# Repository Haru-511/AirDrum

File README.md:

# AirDrum
¿Alguna vez haz querido poder tocar la bateria sin necesidad de tener una bateria?

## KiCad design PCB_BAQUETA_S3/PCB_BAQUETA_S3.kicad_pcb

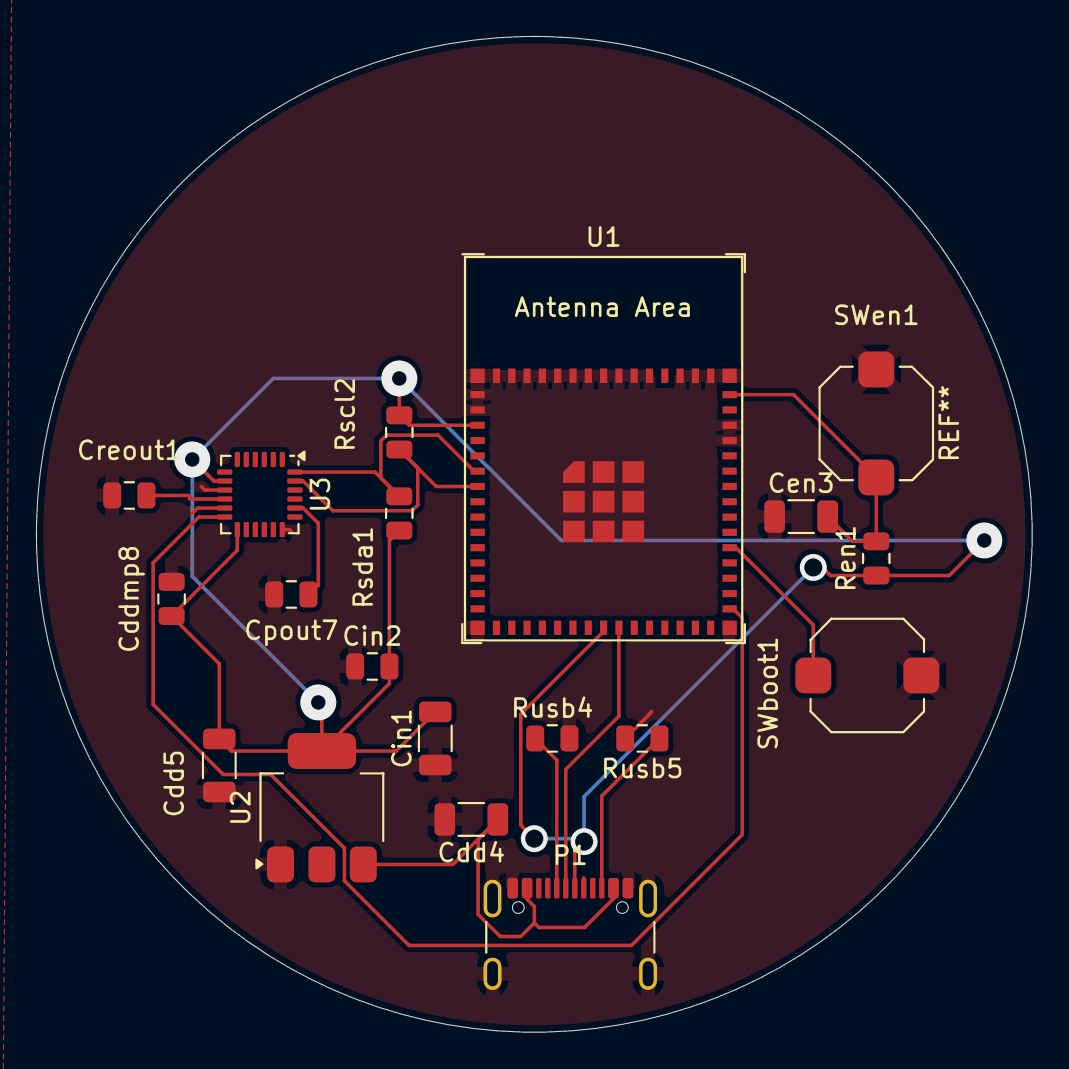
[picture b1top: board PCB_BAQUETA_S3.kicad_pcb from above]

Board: 2 copper layers, 55.3 x 55.3 mm, 19 parts (0 on the bottom side), 13 nets.

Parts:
Cdd4, Cdd5: 22u; C_1206_3216Metric
Cddmp8: 0.1u; C_0805_2012Metric
Cen3: 1u; C_1206_3216Metric
Cin1: 22u; C_1206_3216Metric
Cin2: 0.1; C_0805_2012Metric
Cpout7: 2.2n; C_0805_2012Metric
Creout1: 0.1u; C_0805_2012Metric
P1: USB_C_Plug_USB2.0; USB_C_Receptacle_GCT_USB4105-xx-A_16P_TopMnt_Horizontal
Ren1: 10k; C_0805_2012Metric
Rscl2: 4.7k; C_0805_2012Metric
Rsda1: 4.7k; C_0805_2012Metric
Rusb4, Rusb5: 5.1k; C_0805_2012Metric
SWboot1: SW_Push; SW_Push_1TS009xxxx-xxxx-xxxx_6x6x5mm
SWen1: SW_Push; SW_Push_1TS009xxxx-xxxx-xxxx_6x6x5mm
U1: ESP32-C5-MINI-1
U2: AP1117-33; SOT-223-3_TabPin2
U3: MPU-6050; InvenSense_QFN-24_4x4mm_P0.5mm

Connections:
/D+: P1.A6 (D+), U1.24 (GPIO14/USB_D+)
/D-: Cdd5.1, Cddmp8.1, Cin1.2, Cin2.2, P1.A7 (D-), Ren1.1, Rscl2.1, Rsda1.1, U1.3 (3V3), U1.23 (GPIO13/USB_D-), U2.2 (VO), U3.8 (VLOGIC), U3.13 (VDD)
/EN: Cen3.2, Ren1.2, SWen1.2, U1.45 (EN/CHIP_PU)
/INTERRUPCION: U1.31 (GPIO23), U3.12 (INT)
/SCL: Rscl2.2, U1.7 (GPIO3), U3.23 (SCL)
/SDA: Rsda1.2, U1.6 (GPIO2), U3.24 (SDA)
/V5: Cdd4.1, P1.A4 (VBUS), P1.A9 (VBUS), P1.B4 (VBUS), P1.B9 (VBUS), U2.3 (VI)
GND: Cdd4.2, Cdd5.2, Cddmp8.2, Cen3.1, Cin1.1, Cin2.1, Cpout7.2, Creout1.2, P1.A1 (GND), P1.A12 (GND), P1.B1 (GND), P1.B12 (GND), P1.S1 (SHIELD), Rusb4.2, Rusb5.2, SWboot1.2, SWen1.1, U1.1 (GND), U1.2 (GND), U1.42 (GND), U1.43 (GND), U1.46 (GND), U1.47 (GND), U1.48 (GND), U1.50 (GND), U1.51 (GND), U1.52 (GND), U1.53 (GND), U1.54 (GND), U1.55 (GND), U1.56 (GND), U1.57 (GND), U1.58 (GND), U1.59 (GND), U1.60 (GND), U1.61 (GND), U1.62 (GND), U1.63 (GND), U1.64 (GND), U1.65 (GND), U2.1 (GND), U3.9 (AD0), U3.11 (FSYNC), U3.18 (GND)
unnamed: P1.A5 (CC), Rusb4.1
unnamed: P1.B5 (VCONN), Rusb5.1
unnamed: SWboot1.1, U1.35 (GPIO27)
unnamed: Cpout7.1, U3.20 (CPOUT)
unnamed: Creout1.1, U3.10 (REGOUT)
